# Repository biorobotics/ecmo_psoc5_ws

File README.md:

# ecmo_psoc5_ws
A psoc5 version of ecmo_psoc6_ws to utilize more psoc5/s analog-rich hardware

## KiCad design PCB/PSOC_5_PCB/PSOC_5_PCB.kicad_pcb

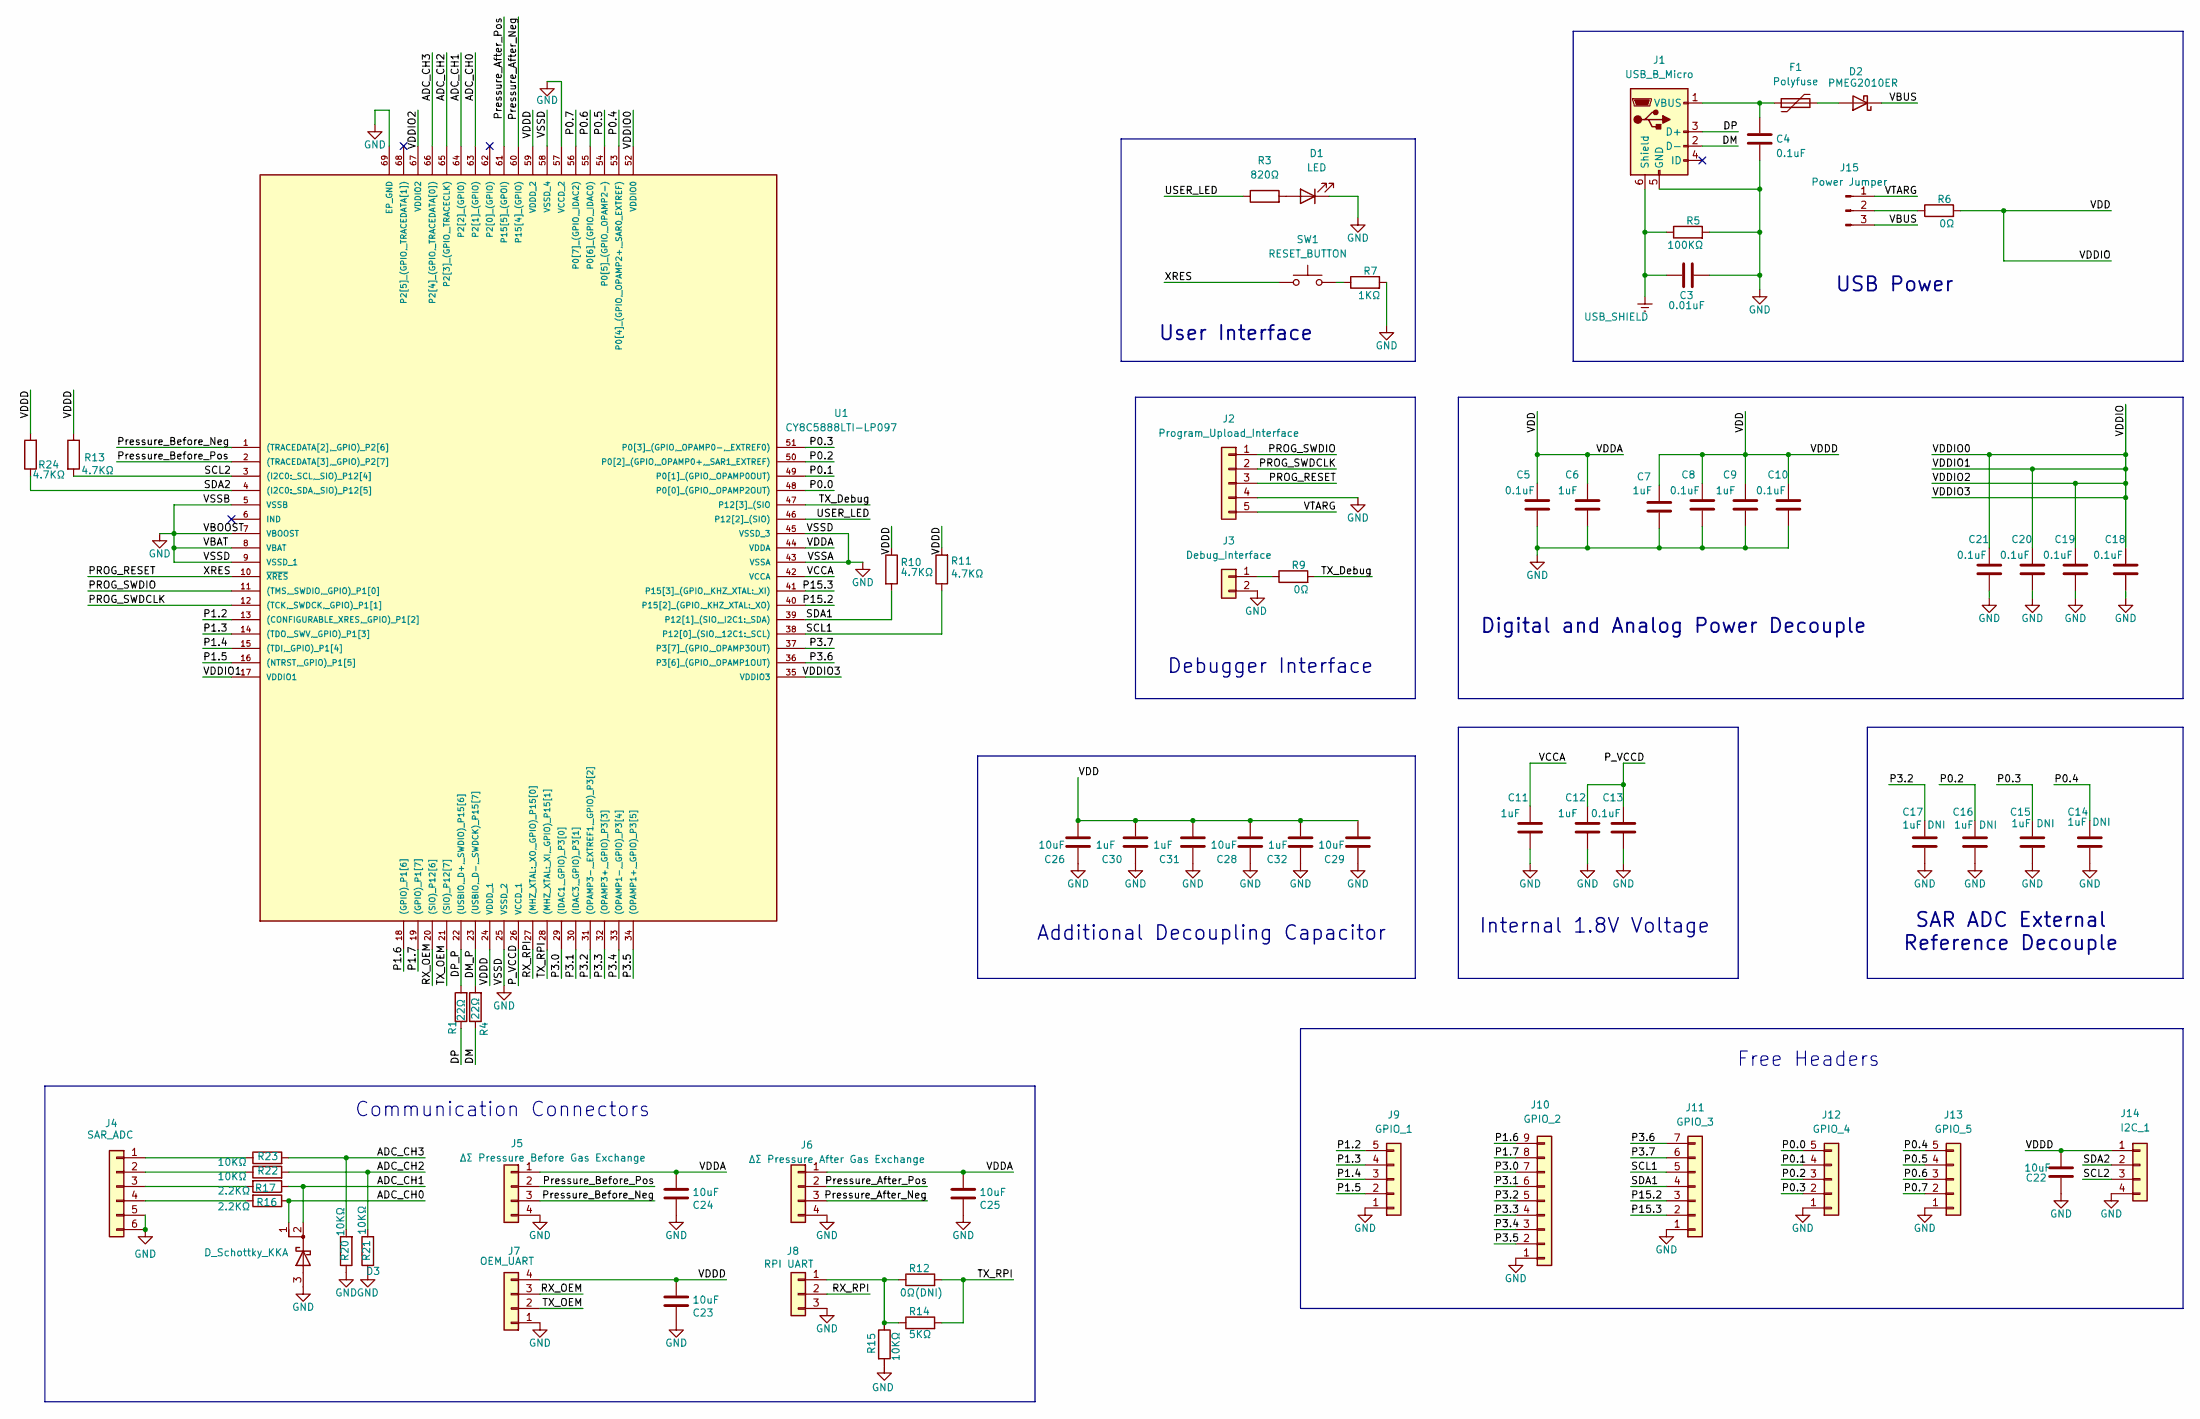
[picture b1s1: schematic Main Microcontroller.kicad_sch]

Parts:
C3: 0.01uF; C_0402_1005Metric
C4, C5, C8, C10, C13, C18, C19, C20, C21: 0.1uF; C_0402_1005Metric
C6, C7, C9, C11, C12: 1uF; C_0402_1005Metric
C14, C15, C16, C17: 1uF DNI; C_0402_1005Metric
C22, C23, C24, C25, C26, C28, C29: 10uF; C_0805_2012Metric
C30, C31, C32: 1uF; C_0603_1608Metric
D1: LED; LED_0805_2012Metric
D2: PMEG2010ER; Nexperia_CFP3_SOD-123W
D3: D_Schottky_KKA; SOT-23
F1: Polyfuse; RESC3216X125N
J1: USB_B_Micro; USB_Micro-B_Amphenol_10118193-0001LF_Horizontal
J2: Program_Upload_Interface; JST_GH_BM05B-GHS-TBT_1x05-1MP_P1.25mm_Vertical
J3: Debug_Interface; JST_GH_BM02B-GHS-TBT_1x02-1MP_P1.25mm_Vertical
J4: SAR_ADC; JST_GH_BM06B-GHS-TBT_1x06-1MP_P1.25mm_Vertical
J5: ΔΣ Pressure Before Gas Exchange; JST_GH_BM04B-GHS-TBT_1x04-1MP_P1.25mm_Vertical
J6: ΔΣ Pressure After Gas Exchange; JST_GH_BM04B-GHS-TBT_1x04-1MP_P1.25mm_Vertical
J7: OEM_UART; JST_GH_BM04B-GHS-TBT_1x04-1MP_P1.25mm_Vertical
J8: RPI UART; JST_GH_BM03B-GHS-TBT_1x03-1MP_P1.25mm_Vertical
J9: GPIO_1; JST_GH_BM05B-GHS-TBT_1x05-1MP_P1.25mm_Vertical
J10: GPIO_2; JST_GH_BM09B-GHS-TBT_1x09-1MP_P1.25mm_Vertical
J11: GPIO_3; JST_GH_BM07B-GHS-TBT_1x07-1MP_P1.25mm_Vertical
J12: GPIO_4; JST_GH_BM05B-GHS-TBT_1x05-1MP_P1.25mm_Vertical
J13: GPIO_5; JST_GH_BM05B-GHS-TBT_1x05-1MP_P1.25mm_Vertical
J14: I2C_1; JST_GH_BM04B-GHS-TBT_1x04-1MP_P1.25mm_Vertical
J15: Power Jumper; PinHeader_1x03_P2.54mm_Vertical
R1, R4: 22Ω; R_0603_1608Metric
R3: 820Ω; R_0603_1608Metric
R5: 100KΩ; R_0402_1005Metric
R6: 0Ω; R_0805_2012Metric
R7: 1KΩ; R_0402_1005Metric
R9: 0Ω; R_0402_1005Metric
R10, R11, R13, R24: 4.7KΩ; R_0603_1608Metric
R12: 0Ω(DNI); R_0402_1005Metric
R14: 5KΩ; R_0402_1005Metric
R15, R20, R21, R22, R23: 10KΩ; R_0402_1005Metric
R16, R17: 2.2KΩ; R_0402_1005Metric
SW1: RESET_BUTTON; SW_SPST_Omron_B3FS-100xP
U1: CY8C5888LTI-LP097; QFN-68; MOUSER_PART_NUMBER 727-CY8C5888LTILP097

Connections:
/Main Microcontroller/ADC_CH0: D3.1 (K), R16.1, U1.63 (P2[1]_(GPIO))
/Main Microcontroller/ADC_CH1: D3.2 (K), R17.1, U1.64 (P2[2]_(GPIO))
/Main Microcontroller/ADC_CH2: R21.2, R22.2, U1.65 (P2[3]_(GPIO,_TRACECLK))
/Main Microcontroller/ADC_CH3: R20.2, R23.2, U1.66 (P2[4]_(GPIO,_TRACEDATA[0]))
/Main Microcontroller/DM: J1.2 (D-), R4.1
/Main Microcontroller/DM_P: R4.2, U1.23 ((USBIO,_D-,_SWDCK)_P15[7])
/Main Microcontroller/DP: J1.3 (D+), R1.1
/Main Microcontroller/DP_P: R1.2, U1.22 ((USBIO,_D+,_SWDIO)_P15[6])
/Main Microcontroller/P0.0: J12.5, U1.48 (P0[0]_(GPIO,_OPAMP2OUT))
/Main Microcontroller/P0.1: J12.4, U1.49 (P0[1]_(GPIO,_OPAMP0OUT))
/Main Microcontroller/P0.2: C16.1, J12.3, U1.50 (P0[2]_(GPIO,_OPAMP0+,_SAR1_EXTREF))
/Main Microcontroller/P0.3: C15.1, J12.2, U1.51 (P0[3]_(GPIO,_OPAMP0-,_EXTREF0))
/Main Microcontroller/P0.4: C14.1, J13.5, U1.53 (P0[4]_(GPIO,_OPAMP2+,_SAR0_EXTREF))
/Main Microcontroller/P0.5: J13.4, U1.54 (P0[5]_(GPIO,_OPAMP2-))
/Main Microcontroller/P0.6: J13.3, U1.55 (P0[6]_(GPIO,_IDAC0))
/Main Microcontroller/P0.7: J13.2, U1.56 (P0[7]_(GPIO,_IDAC2))
/Main Microcontroller/P1.2: J9.5, U1.13 ((CONFIGURABLE_XRES,_GPIO)_P1[2])
/Main Microcontroller/P1.3: J9.4, U1.14 ((TDO,_SWV,_GPIO)_P1[3])
/Main Microcontroller/P1.4: J9.3, U1.15 ((TDI,_GPIO)_P1[4])
/Main Microcontroller/P1.5: J9.2, U1.16 ((NTRST,_GPIO)_P1[5])
/Main Microcontroller/P1.6: J10.9, U1.18 ((GPIO)_P1[6])
/Main Microcontroller/P1.7: J10.8, U1.19 ((GPIO)_P1[7])
/Main Microcontroller/P3.0: J10.7, U1.29 ((IDAC1,_GPIO)_P3[0])
/Main Microcontroller/P3.1: J10.6, U1.30 ((IDAC3,_GPIO)_P3[1])
/Main Microcontroller/P3.2: C17.1, J10.5, U1.31 ((OPAMP3-,_EXTREF1,_GPIO)_P3[2])
/Main Microcontroller/P3.3: J10.4, U1.32 ((OPAMP3+,_GPIO)_P3[3])
/Main Microcontroller/P3.4: J10.3, U1.33 ((OPAMP1-,_GPIO)_P3[4])
/Main Microcontroller/P3.5: J10.2, U1.34 ((OPAMP1+,_GPIO)_P3[5])
/Main Microcontroller/P3.6: J11.7, U1.36 (P3[6]_(GPIO,_OPAMP1OUT))
/Main Microcontroller/P3.7: J11.6, U1.37 (P3[7]_(GPIO,_OPAMP3OUT))
/Main Microcontroller/P15.2: J11.3, U1.40 (P15[2]_(GPIO,_KHZ_XTAL:_XO))
/Main Microcontroller/P15.3: J11.2, U1.41 (P15[3]_(GPIO,_KHZ_XTAL:_XI))
/Main Microcontroller/PROG_RESET: J2.3, SW1.1, U1.10 (~XRES)
/Main Microcontroller/PROG_SWDCLK: J2.2, U1.12 ((TCK,_SWDCK,_GPIO)_P1[1])
/Main Microcontroller/PROG_SWDIO: J2.1, U1.11 ((TMS,_SWDIO,_GPIO)_P1[0])
/Main Microcontroller/P_VCCD: C12.1, C13.1, U1.26 (VCCD_1)
/Main Microcontroller/Pressure_After_Neg: J6.3, U1.60 (P15[4]_(GPIO))
/Main Microcontroller/Pressure_After_Pos: J6.2, U1.61 (P15[5]_(GPOI))
/Main Microcontroller/Pressure_Before_Neg: J5.3, U1.1 ((TRACEDATA[2],_GPIO)_P2[6])
/Main Microcontroller/Pressure_Before_Pos: J5.2, U1.2 ((TRACEDATA[3],_GPIO)_P2[7])
/Main Microcontroller/RX_OEM: J7.3, U1.20 ((SIO)_P12[6])
/Main Microcontroller/RX_RPI: J8.2, U1.27 ((MHZ_XTAL:_XO,_GPIO)_P15[0])
/Main Microcontroller/SCL1: J11.5, R11.1, U1.38 (P12[0]_(SIO,_12C1:_SCL))
/Main Microcontroller/SCL2: J14.3, R13.2, U1.3 ((I2C0:_SCL,_SIO)_P12[4])
/Main Microcontroller/SDA1: J11.4, R10.2, U1.39 (P12[1]_(SIO,_I2C1:_SDA))
/Main Microcontroller/SDA2: J14.2, R24.1, U1.4 ((I2C0:_SDA,_SIO)_P12[5])
/Main Microcontroller/TX_Debug: R9.2, U1.47 (P12[3]_(SIO)
/Main Microcontroller/TX_OEM: J7.2, U1.21 ((SIO)_P12[7])
/Main Microcontroller/TX_RPI: R12.2, R14.2, U1.28 ((MHZ_XTAL:_XI,_GPIO)_P15[1])
/Main Microcontroller/USER_LED: R3.1, U1.46 (P12[2]_(SIO))
/Main Microcontroller/VBUS: D2.1 (K), J15.3
/Main Microcontroller/VCCA: C11.1, U1.42 (VCCA)
/Main Microcontroller/VDD: C5.1, C6.1, C7.1, C8.1, C9.1, C10.1, C18.1, C19.1, C20.1, C21.1, C22.1, C23.1, C24.1, C25.1, C26.1, C28.1, C29.1, C30.1, C31.1, C32.1, J5.1, J6.1, J7.4, J14.1, R6.2, R10.1, R11.2, R13.1, R24.2, U1.17 (VDDIO1), U1.24 (VDDD_1), U1.35 (VDDIO3), U1.44 (VDDA), U1.52 (VDDIO0), U1.59 (VDDD_2), U1.67 (VDDIO2)
/Main Microcontroller/VTARG: J2.5, J15.1
GND: C3.2, C4.2, C5.2, C6.2, C7.2, C8.2, C9.2, C10.2, C11.2, C12.2, C13.2, C14.2, C15.2, C16.2, C17.2, C18.2, C19.2, C20.2, C21.2, C22.2, C23.2, C24.2, C25.2, C26.2, C28.2, C29.2, C30.2, C31.2, C32.2, D1.1 (K), D3.3 (A), J1.5 (GND), J2.4, J3.2, J4.5, J4.6, J5.4, J6.4, J7.1, J8.3, J9.1, J10.1, J11.1, J12.1, J13.1, J14.4, R5.2, R7.2, R15.2, R20.1, R21.1, U1.5 (VSSB), U1.7 (VBOOST), U1.8 (VBAT), U1.9 (VSSD_1), U1.25 (VSSD_2), U1.43 (VSSA), U1.45 (VSSD_3), U1.57 (VCCD_2), U1.58 (VSSD_4), U1.69 (EP_GND)
unnamed: D1.2 (A), R3.2
unnamed: D2.2 (A), F1.2
unnamed: C4.1, F1.1, J1.1 (VBUS)
unnamed: J3.1, R9.1
unnamed: J4.1, R23.1
unnamed: J4.2, R22.1
unnamed: J4.3, R17.2
unnamed: J4.4, R16.2
unnamed: J8.1, R12.1, R14.1, R15.1
unnamed: J15.2, R6.1
unnamed: R7.1, SW1.2
USB_SHIELD: C3.1, J1.6 (Shield), J1.SH, R5.1

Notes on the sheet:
Free Headers
Communication Connectors
Digital and Analog Power Decouple
Debugger Interface
User Interface
Internal 1.8V Voltage
Additional Decoupling Capacitor
USB Power
SAR ADC External Reference Decouple

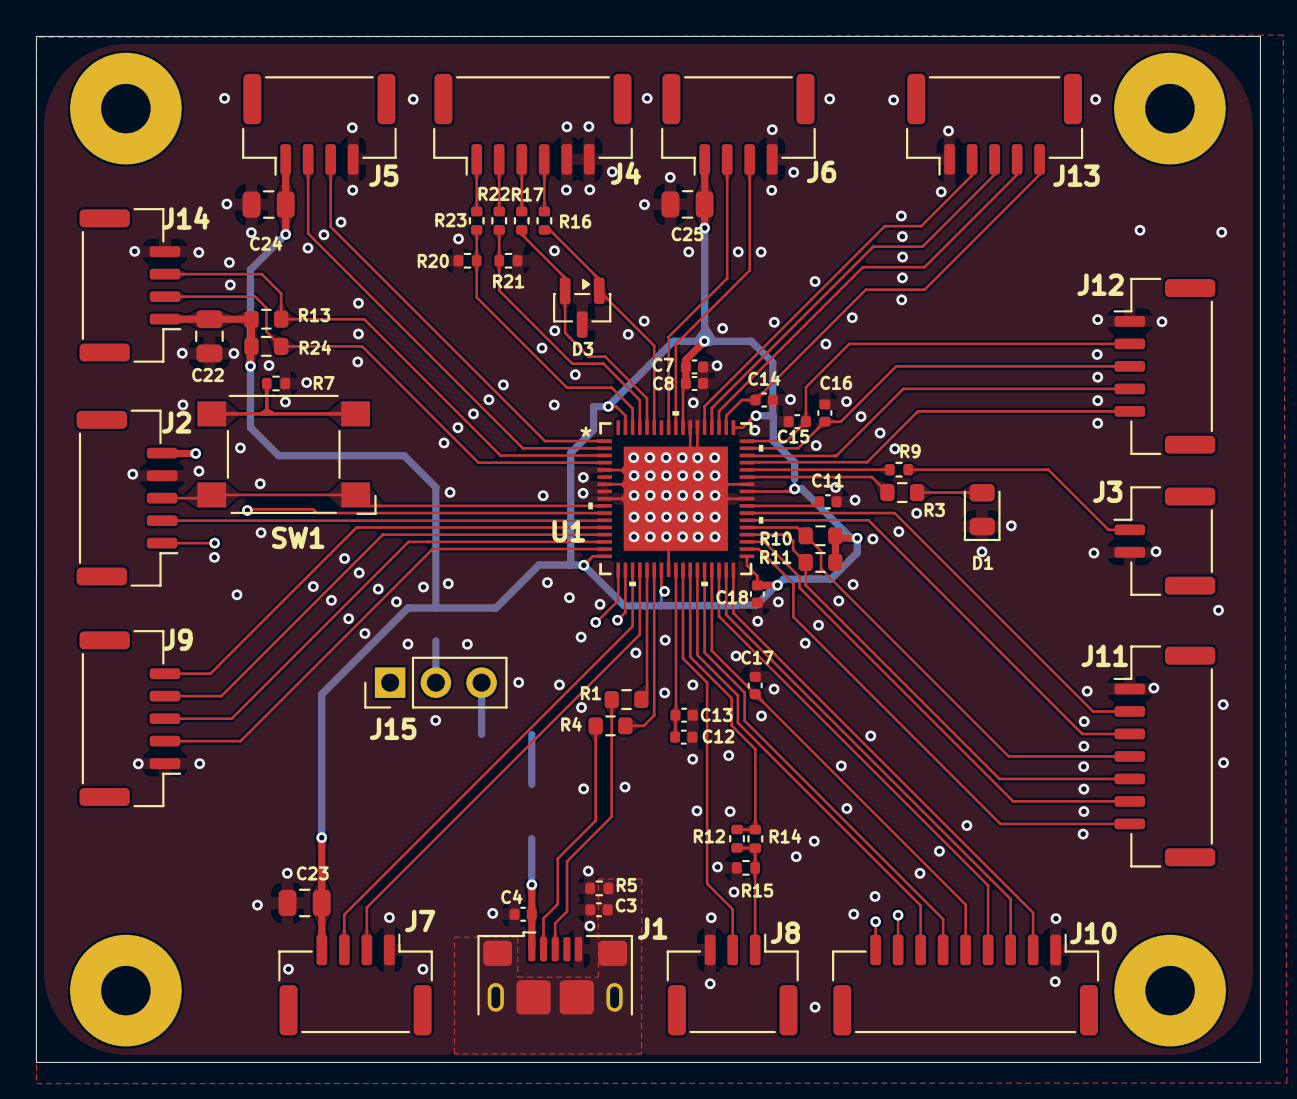
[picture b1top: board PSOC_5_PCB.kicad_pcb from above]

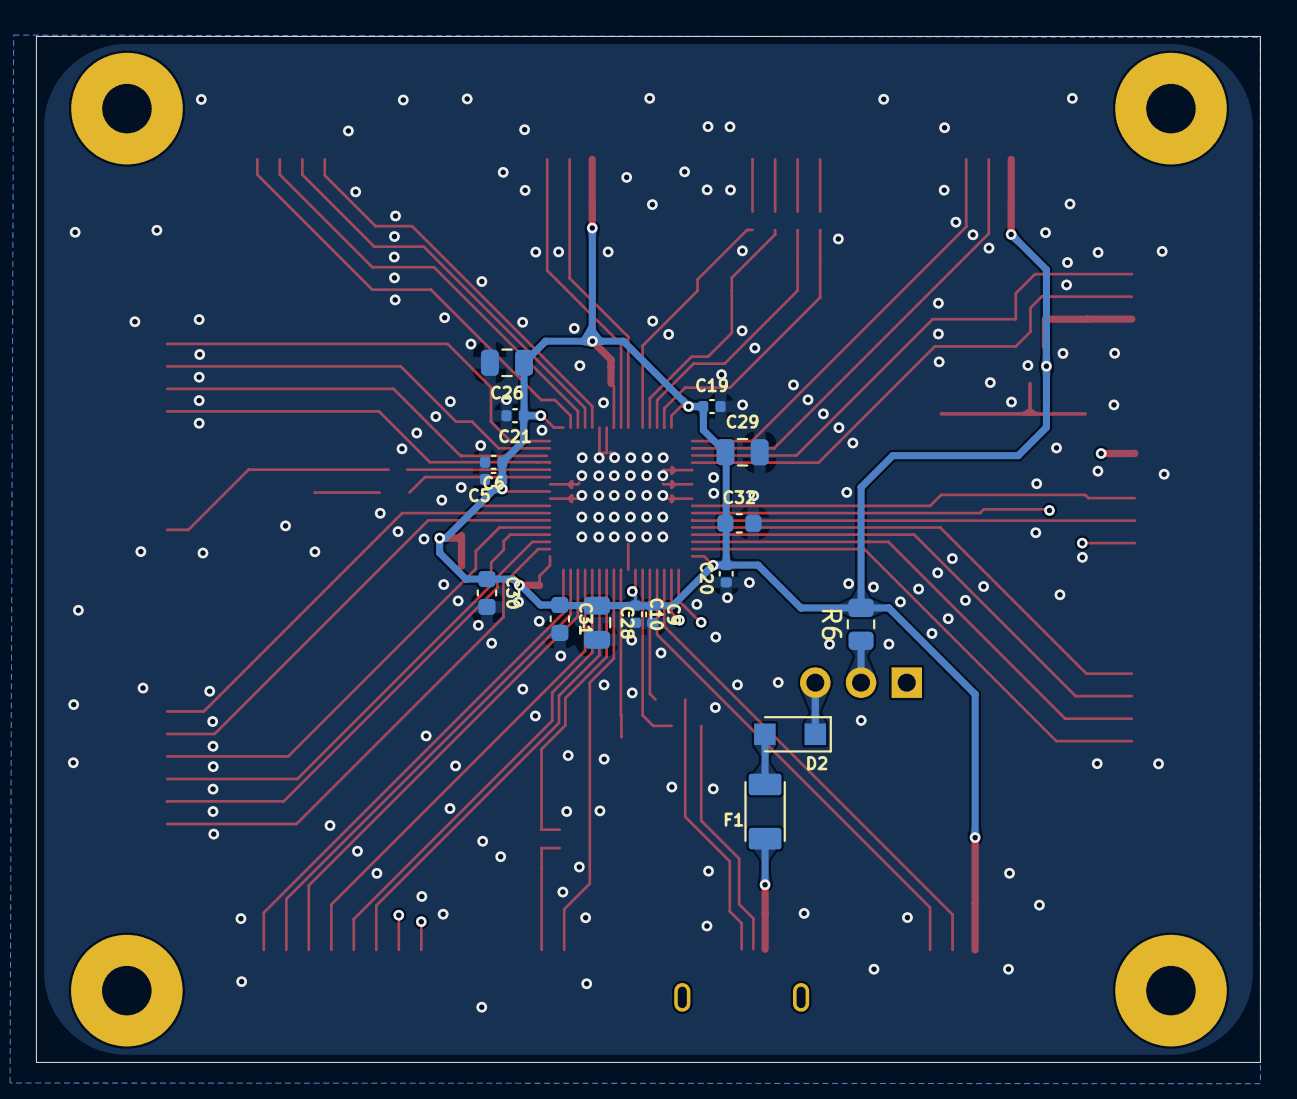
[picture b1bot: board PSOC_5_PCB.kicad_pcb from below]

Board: 4 copper layers, 68.0 x 57.0 mm, 70 parts (16 on the bottom side), 67 nets.

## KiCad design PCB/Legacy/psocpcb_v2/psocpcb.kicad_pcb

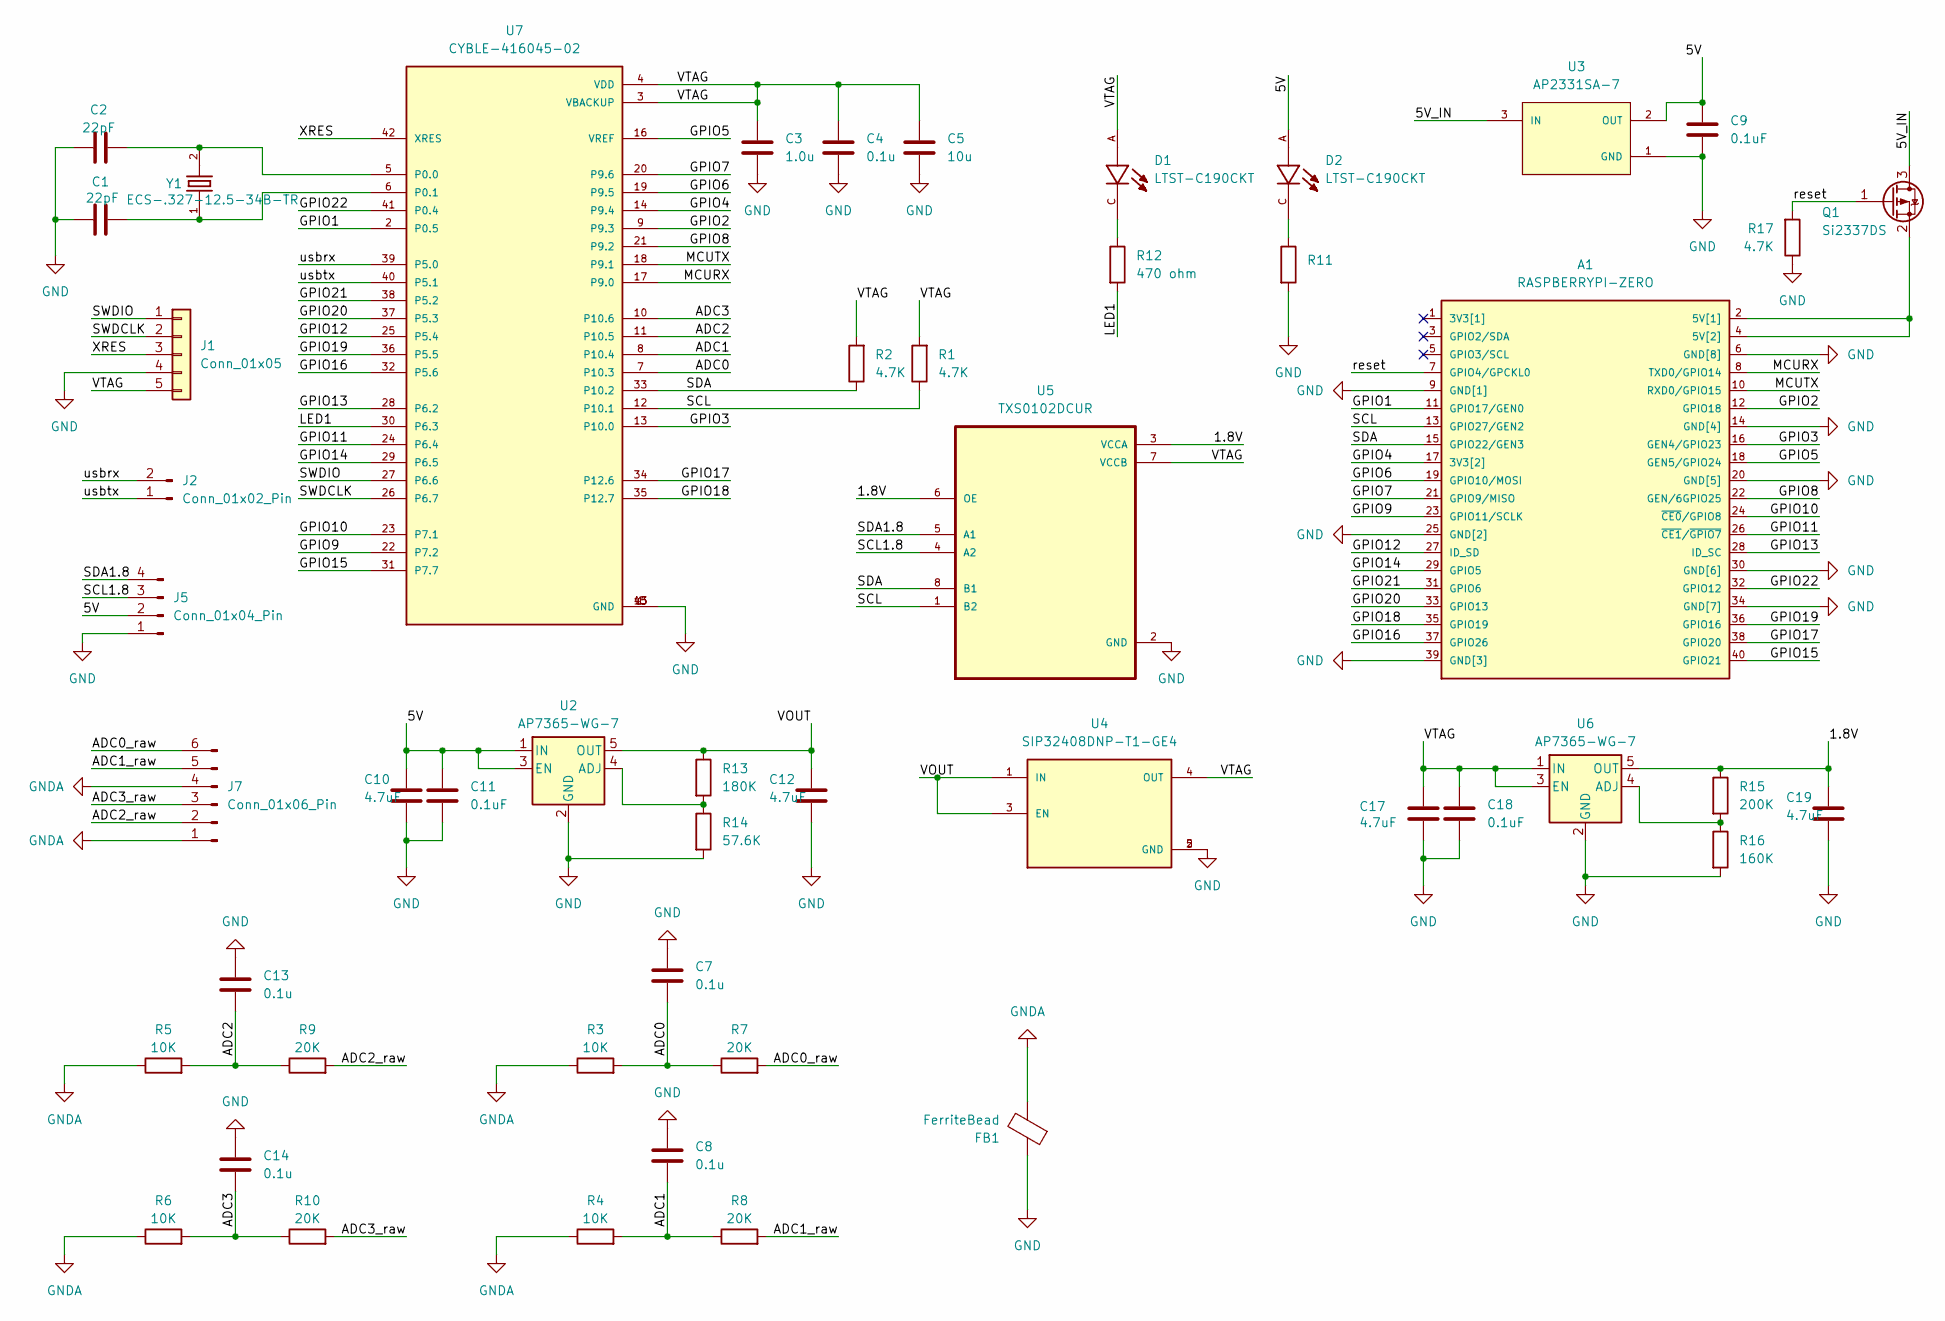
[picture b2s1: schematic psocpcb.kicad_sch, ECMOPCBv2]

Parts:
A1: RASPBERRYPI-ZERO; RASPBERRYPI-ZERO_RPI-ZERO_1
C1, C2: 22pF; C_0603_1608Metric
C3: 1.0u; C_0603_1608Metric
C4, C7, C8, C13, C14: 0.1u; C_0603_1608Metric
C5: 10u; C_0603_1608Metric
C9, C11, C18: 0.1uF; C_0603_1608Metric
C10, C12, C17, C19: 4.7uF; C_0603_1608Metric
D1, D2: LTST-C190CKT; LEDSC160X80X90-2N; PARTREV N/A
FB1: FerriteBead; L_0603_1608Metric
J1: Conn_01x05; PinHeader_1x05_P2.54mm_Vertical
J2: Conn_01x02_Pin; PinHeader_1x02_P2.54mm_Vertical
J5: Conn_01x04_Pin; JST_PH_S4B-PH-K_1x04_P2.00mm_Horizontal
J7: Conn_01x06_Pin; JST_PH_S6B-PH-K_1x06_P2.00mm_Horizontal
Q1: Si2337DS; SOT-23
R1, R2, R17: 4.7K; R_0603_1608Metric
R3, R4, R5, R6: 10K; R_0603_1608Metric
R7, R8, R9, R10: 20K; R_0603_1608Metric
R11: R_0603_1608Metric
R12: 470 ohm; R_0603_1608Metric
R13: 180K; R_0603_1608Metric
R14: 57.6K; R_0603_1608Metric
R15: 200K; R_0603_1608Metric
R16: 160K; R_0603_1608Metric
U2, U6: AP7365-WG-7; SOT95P285X145-5N
U3: AP2331SA-7; SOT91P240X120-3N
U4: SIP32408DNP-T1-GE4; SON50P120X160X60-5N; PARTREV Rev. G
U5: TXS0102DCUR; SOP50P310X90-8N
U7: CYBLE-416045-02; XCVR_CYBLE-416045-02; PARTREV A
Y1: ECS-.327-12.5-34B-TR; XTAL_ECS-.327-12.5-34B-TR

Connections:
/1.8V: C19.1, R15.1, U5.3 (VCCA), U5.6 (OE), U6.5 (OUT)
/5V: C9.1, C10.1, C11.1, D2.A, J5.2, U2.1 (IN), U2.3 (EN), U3.2 (OUT)
/5V_IN: Q1.3 (D), U3.3 (IN)
/ADC0: C7.2, R3.2, R7.1, U7.7 (P10.3)
/ADC0_raw: J7.6, R7.2
/ADC1: C8.2, R4.2, R8.1, U7.8 (P10.4)
/ADC1_raw: J7.5, R8.2
/ADC2: C13.2, R5.2, R9.1, U7.11 (P10.5)
/ADC2_raw: J7.2, R9.2
/ADC3: C14.2, R6.2, R10.1, U7.10 (P10.6)
/ADC3_raw: J7.3, R10.2
/GPIO1: A1.11 (GPIO17/GEN0), U7.2 (P0.5)
/GPIO2: A1.12 (GPIO18), U7.9 (P9.3)
/GPIO3: A1.16 (GEN4/GPIO23), U7.13 (P10.0)
/GPIO4: A1.17 (3V3[2]), U7.14 (P9.4)
/GPIO5: A1.18 (GEN5/GPIO24), U7.16 (VREF)
/GPIO6: A1.19 (GPIO10/MOSI), U7.19 (P9.5)
/GPIO7: A1.21 (GPIO9/MISO), U7.20 (P9.6)
/GPIO8: A1.22 (GEN/6GPIO25), U7.21 (P9.2)
/GPIO9: A1.23 (GPIO11/SCLK), U7.22 (P7.2)
/GPIO10: A1.24 (~CE0/GPIO8), U7.23 (P7.1)
/GPIO11: A1.26 (~CE1/~GPIO7), U7.24 (P6.4)
/GPIO12: A1.27 (ID_SD), U7.25 (P5.4)
/GPIO13: A1.28 (ID_SC), U7.28 (P6.2)
/GPIO14: A1.29 (GPIO5), U7.29 (P6.5)
/GPIO15: A1.40 (GPIO21), U7.31 (P7.7)
/GPIO16: A1.37 (GPIO26), U7.32 (P5.6)
/GPIO17: A1.38 (GPIO20), U7.34 (P12.6)
/GPIO18: A1.35 (GPIO19), U7.35 (P12.7)
/GPIO19: A1.36 (GPIO16), U7.36 (P5.5)
/GPIO20: A1.33 (GPIO13), U7.37 (P5.3)
/GPIO21: A1.31 (GPIO6), U7.38 (P5.2)
/GPIO22: A1.32 (GPIO12), U7.41 (P0.4)
/LED1: R12.2, U7.30 (P6.3)
/MCURX: A1.8 (TXD0/GPIO14), U7.17 (P9.0)
/MCUTX: A1.10 (RXD0/GPIO15), U7.18 (P9.1)
/SCL: A1.13 (GPIO27/GEN2), R1.1, U5.1 (B2), U7.12 (P10.1)
/SCL1.8: J5.3, U5.4 (A2)
/SDA: A1.15 (GPIO22/GEN3), R2.1, U5.8 (B1), U7.33 (P10.2)
/SDA1.8: J5.4, U5.5 (A1)
/SWDCLK: J1.2, U7.26 (P6.7)
/SWDIO: J1.1, U7.27 (P6.6)
/VOUT: C12.1, R13.1, U2.5 (OUT), U4.1 (IN), U4.3 (EN)
/VTAG: C3.1, C4.1, C5.1, C17.1, C18.1, D1.A, J1.5, R1.2, R2.2, U4.4 (OUT), U5.7 (VCCB), U6.1 (IN), U6.3 (EN), U7.3 (VBACKUP), U7.4 (VDD)
/XRES: J1.3, U7.42 (XRES)
/reset: A1.7 (GPIO4/GPCKL0), Q1.1 (G), R17.2
/usbrx: J2.2, U7.39 (P5.0)
/usbtx: J2.1, U7.40 (P5.1)
GND: A1.6 (GND[8]), A1.9 (GND[1]), A1.14 (GND[4]), A1.20 (GND[5]), A1.25 (GND[2]), A1.30 (GND[6]), A1.34 (GND[7]), A1.39 (GND[3]), C1.2, C2.2, C3.2, C4.2, C5.2, C7.1, C8.1, C9.2, C10.2, C11.2, C12.2, C13.1, C14.1, C17.2, C18.2, C19.2, FB1.1, J1.4, J5.1, R11.2, R14.2, R16.2, R17.1, U2.2 (GND), U3.1 (GND), U4.2 (GND), U4.5 (GND), U5.2 (GND), U6.2 (GND), U7.1 (GND), U7.15 (GND), U7.43 (GND)
GNDA: FB1.2, J7.1, J7.4, R3.1, R4.1, R5.1, R6.1
unnamed: A1.2 (5V[1]), A1.4 (5V[2]), Q1.2 (S)
unnamed: D1.C, R12.1
unnamed: D2.C, R11.1
unnamed: R13.2, R14.1, U2.4 (ADJ)
unnamed: R15.2, R16.1, U6.4 (ADJ)
unnamed: C2.1, U7.5 (P0.0), Y1.2
unnamed: C1.1, U7.6 (P0.1), Y1.1

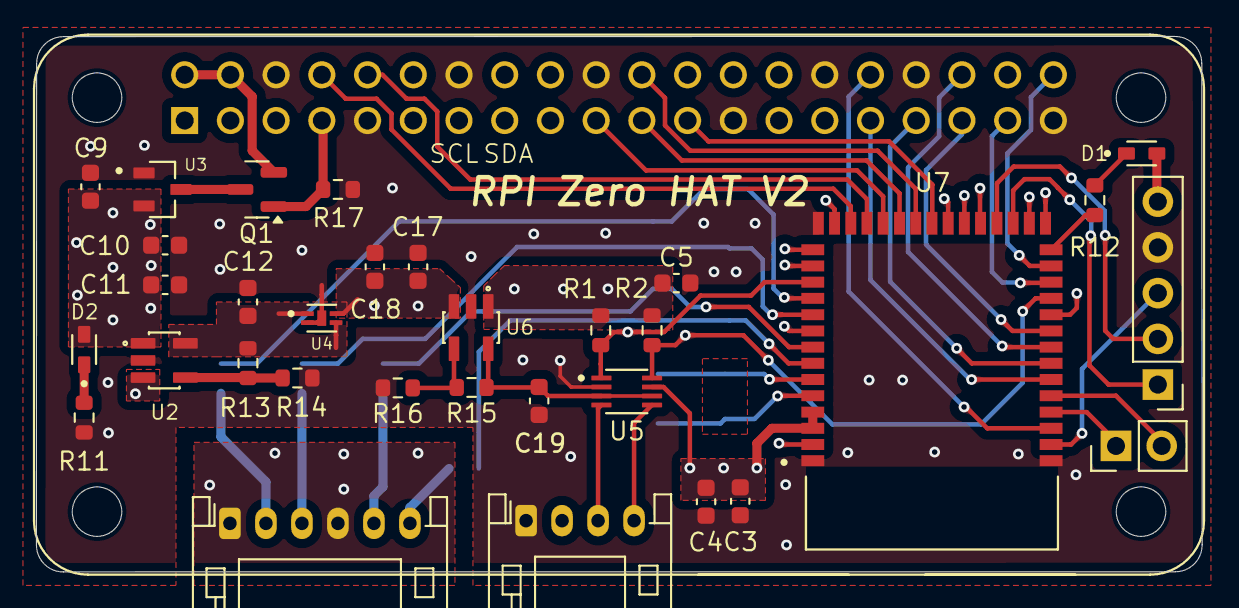
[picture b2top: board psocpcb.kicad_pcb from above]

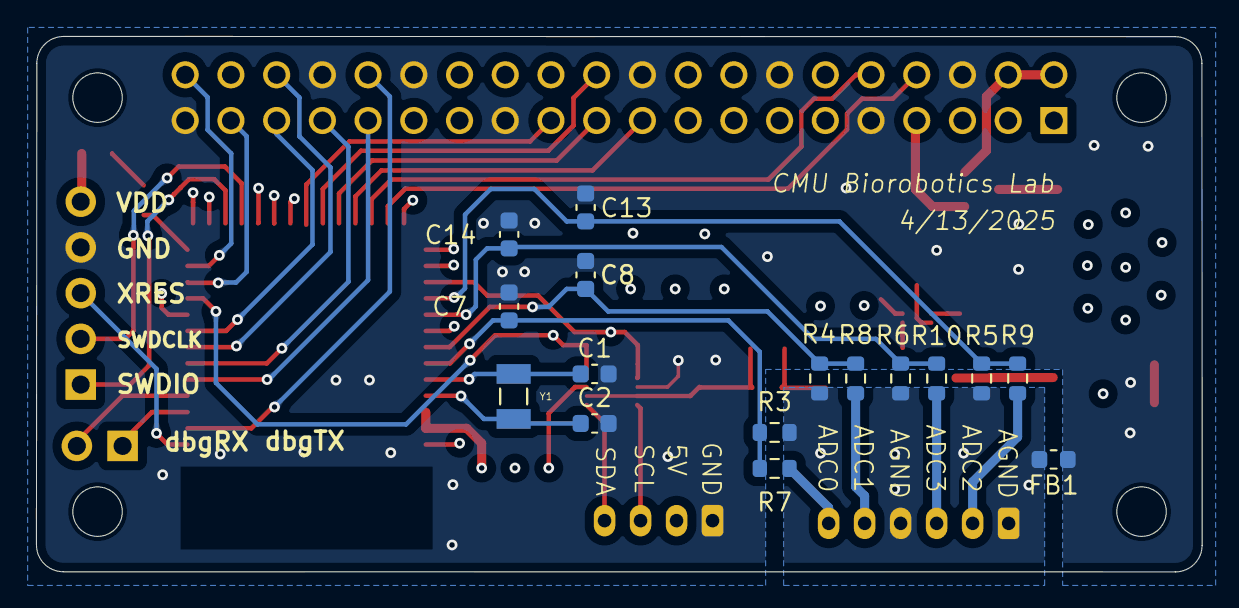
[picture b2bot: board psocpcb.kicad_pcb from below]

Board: 6 copper layers, 64.8 x 29.8 mm, 49 parts (16 on the bottom side), 57 nets.

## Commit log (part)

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2025-09-28 PSoC5 Implement
2025-09-29 Pressure App added
2025-10-01 Software Reset
2025-10-01 Remove Software Reset
2025-10-03 minor change for testing with PSoC5
2025-10-05 PSoC for Flow Sensor UART communication
2025-10-06 bug fix
2025-10-07 Bug fix and change Error Code Format
2025-10-07 Opcode change
2025-10-07 RPi modification for flow sensor
2025-10-07 minor changes in RPi code
2025-10-07 Added questdb reciever
2025-10-08 psoc uart terminator
2025-10-09 changed RPI logging directory
2025-10-09 Working receiver
2025-11-05 Debug Print
2025-11-07 fixing UART bug + PSoC print
2025-11-28 Schematics of New PCB
